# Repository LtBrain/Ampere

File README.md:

# Ampere
A variable benchtop power supply

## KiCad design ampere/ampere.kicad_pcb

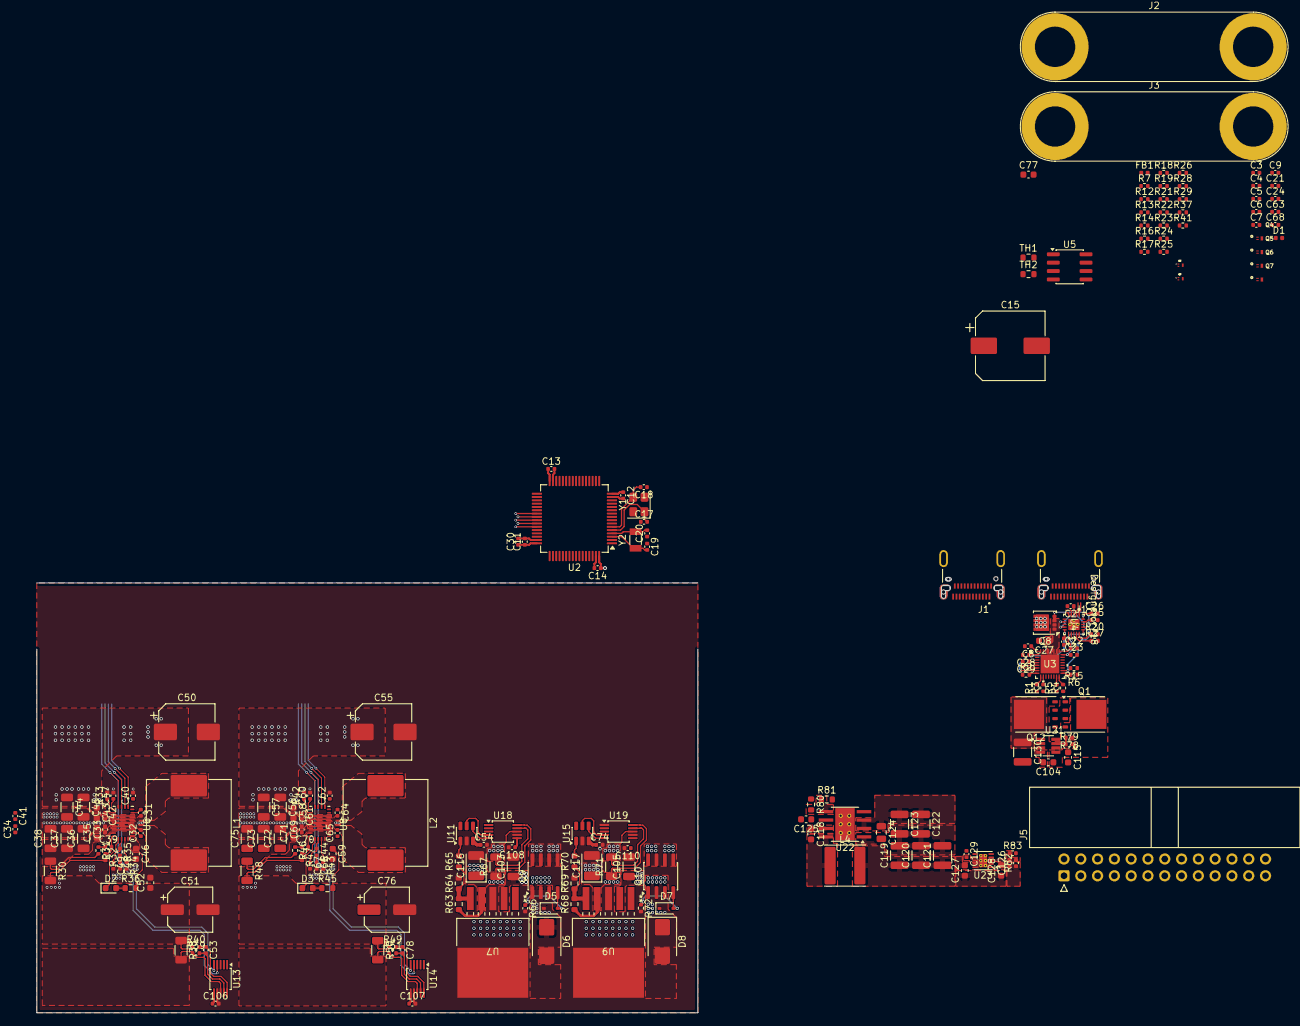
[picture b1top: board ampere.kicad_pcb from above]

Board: 4 copper layers, 211 parts (1 on the bottom side), 124 nets.

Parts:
C1, C9, C11, C12, C13, C14, C21, C24, C25, C26, C31, C32, C33, C34, C39, C40, C41, C42, C53, C54, C61, C62, C63, C64, C65, C68, C69, C70, C74, C78, C106, C107, C108, C110, C129: 100nF; C_0402_1005Metric
C2: 470nF; C_0402_1005Metric
C3: 4.7uF; C_0402_1005Metric
C4, C5, C6, C7, C47, C60, C126: 10nF; C_0402_1005Metric
C8, C28, C29, C30: 10uF; C_0402_1005Metric
C10, C27, C127, C128: 10uF; C_0603_1608Metric
C15: 220uF; CP_Elec_10x10
C17, C18, C19, C20: 18pF; C_0402_1005Metric
C22, C23: 220pF; C_0402_1005Metric
C35, C43, C52, C58, C71, C77, C125: 1uF; C_0603_1608Metric
C36, C37, C38, C44, C45, C56, C57, C72, C73, C75, C103, C105: 10uF; C_1206_3216Metric
C46, C59: 4.7uF; C_0603_1608Metric
C48, C66: 4700pF; C_0402_1005Metric
C49, C67: 100pF; C_0402_1005Metric
C50, C55: 68uF; CP_Elec_8x10
C51, C76: 100uF; CP_Elec_6.3x5.8
C104: 220nF; C_0603_1608Metric
C115, C118: 100nF; C_0603_1608Metric
C116, C117: 10uF; CP_EIA-3528-21_Kemet-B
C119, C120, C121: 22uF; C_1210_3225Metric
C122, C123: 4.7uF; C_1210_3225Metric
C124: 220nF; C_0805_2012Metric
C130: 2.2uF; C_1210_3225Metric
D1: BLUE; LED_0402_1005Metric
D2, D3: RED; LED_0603_1608Metric
D5, D7: 10V; D_SOD-323
D6, D8: SMBJ24CA; D_SMB
FB1: FerriteBead_Small; L_0402_1005Metric
J1, J1#2: USB_C_Receptacle; JAE_DX07S024JJ2R1300
J2: Channel 1; Banana_Jack_2Pin
J3: Channel 2; Banana_Jack_2Pin
J5: Conn_02x13_Odd_Even; IDC-Header_2x13_P2.54mm_Horizontal
L1, L2: 4.7uH; L_Changjiang_FXL1360
L4: 12uH; L_Changjiang_FNR6040S
Q1, Q12: BSC040N08NS5; TDSON-8-1
Q2, Q3: CSD25481F4; TRANS_CSD25481F4
Q4, Q5: CSD13381F4; DFN100X60X35-3N
Q6, Q7: CSD17484F4; DFN100X60X35-3N
Q8: CSD18543Q3A; VSON-8_3.3x3.3mm_P0.65mm_NexFET
Q9, Q10: AO4485; SOIC-8_3.9x4.9mm_P1.27mm
R1, R2, R4, R5: 2.2K; R_0402_1005Metric
R3, R6, R14, R72: 10K; R_0402_1005Metric
R7, R15, R16, R18, R28, R29, R37, R41, R78: 100K; R_0402_1005Metric
R12, R13, R20, R21, R22, R23, R26, R27: 0; R_0402_1005Metric
R17, R19, R24, R25: 1M; R_0402_1005Metric
R30, R38, R48, R50, R67, R71: 10m; R_1206_3216Metric
R31, R32, R39, R40, R46, R47, R49, R51: 10; R_0402_1005Metric
R33, R42: 49.9K; R_0402_1005Metric
R34, R43: 150K; R_0402_1005Metric
R35, R44: 27.4K; R_0402_1005Metric
R36, R45: 2.2K; R_0603_1608Metric
R63, R68: 9.2K; R_0603_1608Metric
R64, R69: 1K; R_0603_1608Metric
R65, R70: 1.56K; R_0603_1608Metric
R66: 10K; C_0402_1005Metric
R79: 4K; R_0402_1005Metric
R80: 100K; R_0603_1608Metric
R81: 38.2K; R_0603_1608Metric
R82: 100K; C_0402_1005Metric
R83: 32.4K; C_0402_1005Metric
TH1, TH2: Thermistor; R_0603_1608Metric
U2: STM32G474RETx; LQFP-64_10x10mm_P0.5mm
U3: TPS26750SRSMR; VQFN32_RSM_TEX-L
U4: TPD4S480RUKR; RUK0020B-MFG
U5: CAT24C256; SOIC-8_3.9x4.9mm_P1.27mm
U6, U8: TPS55289; CONV_TPS552892RYQR
U7, U9: MIC29302WU; TO-263-5_ET_DDPAK_MCH
U11, U15: MCP4725xxx-xCH; SOT-23-6
U13, U14, U18, U19: INA238; TSSOP-10_3x3mm_P0.5mm
U21: LM74502DDFR; SOT65P280X110-8N
U22: LMR36520ADDA; Texas_HTSOP-8-1EP_3.9x4.9mm_P1.27mm_EP2.95x4.9mm_Mask2.4x3.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
U23: TPS7A91; Texas_S-PDSO-N10_EP1.2x2mm_ThermalVias
Y1: 25 MHZ; Crystal_SMD_3225-4Pin_3.2x2.5mm
Y2: 32.768 KHZ; Crystal_SMD_3215-2Pin_3.2x1.5mm

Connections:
3V6: C119.1, C120.1, C121.1, C127.2, L4.2, R80.1, U23.6 (SS_CTRL), U23.7 (EN), U23.9 (IN), U23.10 (IN)
5V_VCC: C46.1, C59.1, R36.2, R45.2, U6.18 (VCC), U8.18 (VCC)
/CC1: C23.1, U3.24 (CC1), U4.12 (CC1)
/CC2: C22.1, U3.25 (CC2), U4.11 (CC2)
/GPIO2: U3.7 (GPIO2), U4.16 (EPR_EN)
/GPIO3: R15.2, U3.18 (GPIO3), U4.9 (FLT_N)
/GPIO4: R21.1, U3.22 (GPIO4/USB_P/LD1)
/GPIO5: R26.1, U3.23 (GPIO5/USB_N/LD2)
/GPIO6: R22.1, U3.31 (GPIO6)
/GPIO7: R23.1, U3.30 (GPIO7)
/GPIO_NF: Q4.1 (G), Q5.1 (G), R18.2, R23.2
/GPIO_PF: Q2.1 (G), Q3.1 (G), R16.2, R22.2
/MODE: U6.2 (MODE), U8.2 (MODE)
/PWRPATH_EN: Q6.1 (G), U3.20 (POWER_PATH_EN)
/SBU1: R20.1, U4.15 (SBU1)
/SBU2: R27.1, U4.14 (SBU2)
/SENSE1+: C116.1, R63.1, R67.1, U7.4 (VOUT), U18.10 (Vin+)
/SENSE1-: Q9.5 (D), Q9.6 (D), Q9.7 (D), Q9.8 (D), R67.2, U18.8 (Vbus), U18.9 (Vin-)
/SENSE2+: C117.1, R68.1, R71.1, U9.4 (VOUT), U19.10 (Vin+)
/SENSE2-: Q10.5 (D), Q10.6 (D), Q10.7 (D), Q10.8 (D), R71.2, U19.8 (Vbus), U19.9 (Vin-)
CH1_EN: R37.2, U6.1 (EN/UVLO)
CH1_SCL: U2.43 (I2C2_SCL), U6.3 (SCL), U13.5 (SCL), U15.5 (SCL), U19.4 (SDA)
CH1_SDA: U2.42 (I2C2_SDA), U6.4 (SDA), U13.4 (SDA), U15.4 (SDA), U19.5 (SCL)
CH2_EN: R41.2, U8.1 (EN/UVLO)
CH2_SCL: U2.40 (I2C3_SCL), U8.3 (SCL), U14.5 (SCL)
CH2_SDA: U2.41 (I2C3_SDA), U8.4 (SDA), U14.4 (SDA)
CH3_SCL: U2.38 (I2C4_SCL), U11.5 (SCL), U18.4 (SDA)
CH3_SDA: U2.39 (I2C4_SDA), U11.4 (SDA), U18.5 (SCL)
C_CC1: J1#2.A5 (CC1), R12.2, U4.4 (C_CC1)
C_CC2: J1#2.B5 (CC2), R13.2, U4.5 (C_CC2)
C_SBU1: J1#2.A8 (SBU1), U4.1 (C_SBU1)
C_SBU2: J1#2.B8 (SBU2), U4.2 (C_SBU2)
EXTVCC: C40.1, C62.1, U6.21 (EXTVCC), U8.21 (EXTVCC)
GND: C1.2, C2.2, C3.2, C4.2, C5.2, C6.2, C7.2, C8.2, C9.2, C10.2, C11.2, C12.2, C13.2, C14.2, C15.2, C17.1, C18.1, C19.1, C20.1, C21.2, C22.2, C23.2, C24.2, C25.2, C26.2, C27.2, C28.2, C29.2, C30.2, C33.2, C34.2, C35.2, C36.2, C37.2, C38.2, C40.2, C41.2, C42.2, C43.2, C44.2, C45.2, C46.2, C47.2, C48.2, C49.2, C50.2, C51.2, C52.2, C54.2, C55.2, C56.2, C57.2, C58.2, C59.2, C60.2, C61.2, C62.2, C63.2, C66.2, C67.2, C68.2, C69.2, C71.2, C72.2, C73.2, C74.2, C75.2, C76.2, C77.2, C103.2, C105.2, C106.2, C107.2, C108.2, C110.2, C115.2, C116.2, C117.2, C119.2, C120.2, C121.2, C122.2, C123.2, C124.2, C125.2, C127.1, C128.1, C129.1, C130.2, D6.2 (A2), D8.2 (A2), J1#2.A1 (GND), J1#2.A12 (GND), J1#2.B1 (GND), J1#2.B12 (GND), J2.2, J3.2, Q4.2 (S), Q5.2 (S), Q6.2 (S), Q7.2 (S), R14.2, R18.1, R33.2, R34.2, R37.1, R41.1, R42.2, R43.2, R64.2, R66.2, R69.2, R72.2, R79.2, R81.2, R83.2, U2.15 (VSS), U2.27 (VSSA), U2.31 (VSS), U2.47 (VSS), U2.63 (VSS), U3.2 (ADCIN1), U3.3 (ADCIN2), U3.11 (GND), U3.12 (GND), U3.14 (GND), U3.19 (GND), U3.33 (GND), U4.8 (GND), U4.13 (GND), U4.18 (GND), U4.21 (Thermal_Pad), U5.1 (A0), U5.2 (A1), U5.3 (A2), U5.4 (GND), U5.7 (WP), U6.9 (PGND), U6.17 (AGND), U7.3 (GND), U8.9 (PGND), U8.17 (AGND), U9.3 (GND), U11.2 (VSS), U13.7 (GND), U14.7 (GND), U15.2 (VSS), U18.7 (GND), U19.1 (A1), U19.7 (GND), U21.2 (GND), U22.1 (PGND), U22.9 (PAD), U23.4 (GND), U23.11 (GND), Y1.2 (G), Y1.4 (G)
I2CC_IRQ: R6.2, U3.17 (*I2CC_IRQ)
I2CC_SCL: R4.2, U3.16 (I2CC_SCL), U5.6 (SCL)
I2CC_SDA: R5.2, R7.2, U3.15 (I2CC_SDA), U5.5 (SDA)
I2CT_IRQ: R3.2, U3.10 (*I2CT_IRQ)
I2CT_SCL: R1.2, U3.9 (I2CT_SCL)
I2CT_SDA: R2.2, U3.8 (I2CT_SDA)
LDO1_VOUT: D5.1 (K), D6.1 (A1), Q9.1 (S), Q9.2 (S), Q9.3 (S)
LDO2_VOUT: D7.1 (K), D8.1 (A1), Q10.1 (S), Q10.2 (S), Q10.3 (S)
LDO_1V5: C29.1, U3.4 (LDO_1V5)
LDO_3V3: C1.1, C24.1, C28.1, Q2.2 (S), Q3.2 (S), R1.1, R2.1, R3.1, R4.1, R5.1, R6.1, R7.1, R15.1, R16.1, R28.1, R29.1, U3.1 (LDO_3V3), U4.10 (VPWR), U5.8 (VCC)
LDO_VIN: C76.1, C77.1, C103.1, C105.1, R47.2, R48.2, R49.1, R50.1, U7.2 (VIN), U9.2 (VIN)
MCU_VDD: C11.1, C12.1, C13.1, C14.1, C30.1, C54.1, C74.1, C106.1, C107.1, C108.1, C110.1, C126.1, C128.2, R82.1, U2.16 (VDD), U2.32 (VDD), U2.48 (VDD), U2.64 (VDD), U11.3 (VDD), U13.6 (VS), U14.6 (VS), U15.3 (VDD), U18.6 (VS), U19.6 (VS), U23.1 (OUT), U23.2 (OUT)
unnamed: C48.1, R35.2
unnamed: C51.1, C52.1, R30.2, R32.2, R38.1, R40.1
unnamed: C66.1, R44.2
unnamed: D1.1 (K), R14.1
unnamed: D2.2 (A), R36.1
unnamed: D2.1 (K), U6.14 (FB)
unnamed: D3.2 (A), R45.1
unnamed: D3.1 (K), U8.14 (FB)
unnamed: D5.2 (A), Q9.4 (G), R66.1
unnamed: D7.2 (A), Q10.4 (G), R72.1
unnamed: J2.1, R38.2, R39.1, U13.8 (Vbus)
unnamed: J3.1, R50.2, R51.1, U14.8 (Vbus)
unnamed: Q1.4 (G), Q12.4 (G), U21.6 (GATE)
unnamed: Q2.3 (D), R17.1
unnamed: Q3.3 (D), R24.1
unnamed: Q4.3 (D), R19.2
unnamed: Q5.3 (D), R25.2
unnamed: Q6.3 (D), Q7.1 (G), R28.2
unnamed: Q8.4 (G), U4.17 (EPR_BLK_G)
unnamed: R17.2, R19.1, R20.2, R21.2
unnamed: R24.2, R25.1, R26.2, R27.2
unnamed: R12.1, U4.7 (RPD_G1)
unnamed: R13.1, U4.6 (RPD_G2)
unnamed: C2.1, U4.3 (VBIAS)
unnamed: C31.1, U6.20 (BOOT1)
unnamed: C32.1, U6.19 (BOOT2)
unnamed: R34.1, U6.16 (CDC)
unnamed: C49.1, R35.1, U6.15 (COMP)
unnamed: C47.1, U6.5 (DITH/SYNC)
unnamed: R33.1, U6.6 (FSW)
unnamed: C39.2, R32.1, U6.13 (ISN)
unnamed: C39.1, R31.1, U6.12 (ISP)
unnamed: C31.2, L1.1, U6.8 (SW1)
unnamed: C32.2, L1.2, U6.10 (SW2)
unnamed: C33.1, C34.1, C35.1, C36.1, C37.1, C38.1, R30.1, R31.2, U6.11 (VOUT)
unnamed: R63.2, R64.1, R65.1, U7.5 (ADJ)
unnamed: C64.1, U8.20 (BOOT1)
unnamed: C65.1, U8.19 (BOOT2)
unnamed: R43.1, U8.16 (CDC)
unnamed: C67.1, R44.1, U8.15 (COMP)
unnamed: C60.1, U8.5 (DITH/SYNC)
unnamed: R42.1, U8.6 (FSW)
unnamed: C70.2, R47.1, U8.13 (ISN)
unnamed: C70.1, R46.1, U8.12 (ISP)
unnamed: C64.2, L2.1, U8.8 (SW1)
unnamed: C65.2, L2.2, U8.10 (SW2)
unnamed: C68.1, C69.1, C71.1, C72.1, C73.1, C75.1, R46.2, R48.1, U8.11 (VOUT)
unnamed: R68.2, R69.1, R70.1, U9.5 (ADJ)
unnamed: R65.2, U11.1 (VOUT)
unnamed: C53.1, R40.2, U13.10 (Vin+)
unnamed: C53.2, R39.2, U13.9 (Vin-)
unnamed: C78.1, R49.2, U14.10 (Vin+)
unnamed: C78.2, R51.2, U14.9 (Vin-)
unnamed: R70.2, U15.1 (VOUT)
unnamed: R78.2, R79.1, U21.7 (OV)
unnamed: Q1.1 (S), Q1.2 (S), Q1.3 (S), Q12.1 (S), Q12.2 (S), Q12.3 (S), U21.8 (SRC)
unnamed: C104.2, U21.4 (VCAP)
unnamed: C118.1, U22.7 (BOOT)
unnamed: R80.2, R81.1, U22.5 (FB)
unnamed: C118.2, L4.1, U22.8 (SW)
unnamed: C125.1, U22.6 (VCC)
unnamed: C126.2, R82.2, R83.1, U23.3 (FB)
unnamed: C129.2, U23.8 (NR/SS)
PP5V: C10.1, C27.1, U3.28 (PP5V), U3.29 (PP5V)
PPHV: C15.1, C122.1, C123.1, C124.1, C130.1, Q12.5 (D), U22.2 (VIN), U22.3 (EN)
PP_EN: Q7.3 (D), R29.2, U21.1 (EN/UVLO)
RCC_OSC_IN: C17.2, U2.5 (RCC_OSC_IN), Y1.1
RCC_OSC_OUT: C18.2, U2.6 (RCC_OSC_OUT), Y1.3
RTC_OSC_IN: C19.2, U2.3 (RCC_OSC32_IN), Y2.2
RTC_OSC_OUT: C20.2, U2.4 (RCC_OSC32_OUT), Y2.1
USB_DM: J1#2.A7 (D-), J1#2.B7 (D-), U2.45 (USB_DM)
USB_DP: J1#2.A6 (D+), J1#2.B6 (D+), U2.46 (USB_DP)
VBUS: C26.1, C104.1, C115.1, D1.2 (A), FB1.1, Q1.5 (D), Q8.5 (D), R78.1, U4.20 (VBUS), U21.5 (VS)
VBUS_C: C3.1, C4.1, C5.1, C6.1, C7.1, FB1.2, J1#2.A4 (VBUS), J1#2.A9 (VBUS), J1#2.B4 (VBUS), J1#2.B9 (VBUS)
VBUS_LV: C9.1, C25.1, Q8.1 (S), Q8.2 (S), Q8.3 (S), U3.26 (VBUS), U3.27 (VBUS), U4.19 (VBUS_LV)
VIN: C41.1, C42.1, C43.1, C44.1, C45.1, C50.1, C55.1, C56.1, C57.1, C58.1, C61.1, C63.1, U6.7 (VIN), U8.7 (VIN)
VIN_3V3: C8.1, U3.32 (VIN_3V3)
VREF+: C21.1, U2.28 (VREF+)
